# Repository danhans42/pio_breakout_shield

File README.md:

# pio_breakout_shield

Simple shield for a 39SF020, CH375/6 and Atmel ATF22V10 - for use on a Sony PlayStation console for expansion experimentation. Pretty much the basis for a modern replacement PIO cart. The parts used are(were?) easily obtainable from your online marketplace of choice.

PCB's
=====

PCB's - I used JLCPCB for production and found them very well priced, with quick delivery to me (UK). Quality was also very good, Files are provided here for the shield itself, the breakout PCB files are available on the pcsx repo - see further down this document.

Example configuration - 'fully loaded'

Parts List
==========

- SST39SF020 EEPROM (2Megabit)
- WCH 375/376 module (Either works - 376 is better as it has FAT/FAT32 support)
- Atmel ATF22V10C SPLD (GAL/PAL like device)
- 7805 type 5v regulator (i used a little module for efficiency)
- few caps for decoupling
- DIP32 socket
- PCB Pins - enough to join the bords together or use your own solution
- 68 way expansion connector (see later on for details)

When fitting the CH Module - you will notice that the connector is not correctly placed to allow for correct connection, the connect must be removed from the module and soldered from the beneath. See the image above.

PIO Breakout
============

PIO-Breakout is a seperate PCB (https://github.com/grumpycoders/pcsx-redux/wiki/PIO-Breakout), part of the PCSX-Redux project - https://pcsx-redux.consoledev.net/ which this board is designed to plug onto. You can find the files for the pcb in the repository.

The breakout board is great for expansion experimentation and highly recomended.

PIO Connector
=============

The PIO connectors can be difficult to source. See the information in the pcsx-redux wiki on the subject here, https://github.com/grumpycoders/pcsx-redux/wiki/PIO-port-replacement. Digikey link https://www.digikey.co.uk/en/products/detail/molex/0015921468/480913. They are also available on AliExpress for around $1.80 (link to follow). They do however require modification with a dremel slightly.

Alternatively if you are desperate you can source one from a faulty HK AR clone or such,

pio_breakout_shield Configuration
=================================

The board that be populated as much or as little as required. It can provide a simple 256k boot ROM so the PlayStation can boot from it - handy for Unirom etc. Alternatively you can add/program the SPLD (ATF22v10C), add a CH375/6 to it and you have a bootable cartridge that allows for USB host/device experimentation. 

The provided config (PSX_PLORER in \atf22v10c folder) for the SPLD provides the following :- 

- 256k flash @ 0x1f000000 in one block (like xplorer)
- CH37x @ 0x1f060002 (data)/0x1f060003 (cmd)
- rom enable jumper (bridge) IO15/IO14 (useful if you screw up the rom and want to recover without cart hotswapping)

This is very basic, its my intention to add some form of GPIO via the remaining pins but I currently do not have the patience with WinCUPL.
If you so chose, you could fit a 29EE020 and be able to use the standard xplorer firmware (non pro/fx) with this config.

The CH-375 supports usb device(CH372) and host mode for mass storage. However the CH376 in addition has built in FAT16/32 file system support. In future I will upload some source examples for host most such as USB Mouse examples etc. and for mass storage. 

ATF22V10C Programming
=====================

The ATF22v10c can be programmed with a TL866 programmer, as can the EEPROM itself. If you wish to play around with the configuration of the SPLD you will need to obtain WinCUPL (https://www.microchip.com/en-us/products/fpgas-and-plds/spld-cplds/pld-design-resources) to build your own equations. Unfortunately I do not know of a modern, open-source equivalent to work with these parts. Ideally use Windows or it can be got to work with Wine, as can the TL866 software.

Alternatively you can just burn the provided jed which will give you the default configuration which is similar in layout to a 256k Xplorer with the addition of the USB in the space above the ROM. (todo - document address layout). The source is provided. Its initially quite basic in scope but want to add to it to make use of the expansion IO connections provided, as well as switch functionality if desired.

Credit and Thanks
=================

To note: the PCB layout and design is the work of Nicolas Noble who was kind enough to design this for me. Thanks for this and the PIO-Breakout, without none of this would have been possible. Same for UNIROM (thanks sickle) which is indispensable for easy debugging of hardware like this. 

For more info or psx related chat - join us on psx.dev discord (http://psx.dev/)

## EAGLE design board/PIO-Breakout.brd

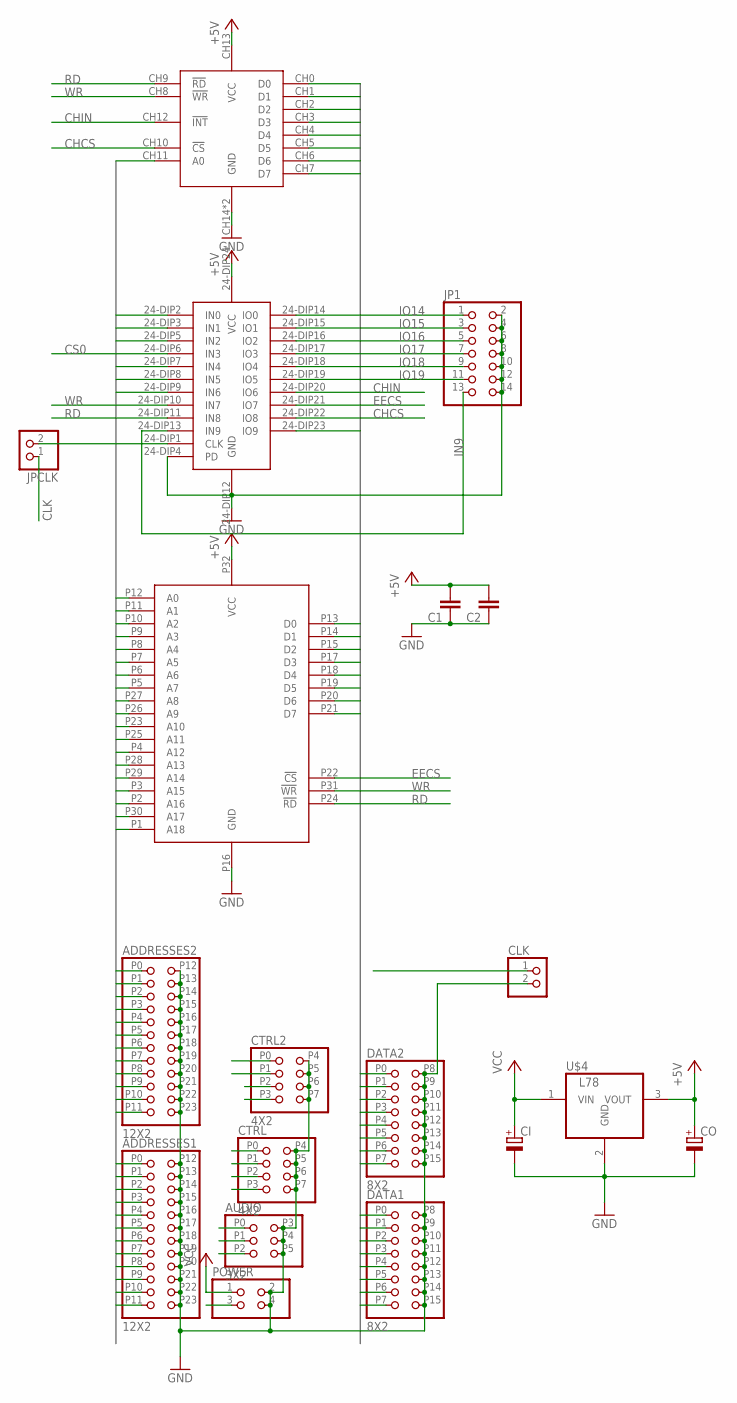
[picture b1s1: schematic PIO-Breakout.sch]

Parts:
ADDRESSES1, ADDRESSES2: 12X2
AUDIO: 3X2
C1, C2: C-EU025-024X044; C025-024X044
CI: CPOL-EUE2,5-6E; E2,5-6E
CLK: PINHD-1X2; 1X02
CO: CPOL-EUE2,5-6E; E2,5-6E
CTRL, CTRL2: 4X2
DATA1, DATA2: 8X2
JP1: PINHD-2X7; 2X07
JPCLK: PINHD-1X2; 1X02
POWER: PINHD-2X2; 2X02
U$1: AT29C040A; DIP-32
U$2: ATF22V10C-10PU; 24-DIP
U$3: CH375B-BOARD
U$4: L78; TO-220-HEATSINK

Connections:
+3V3: POWER.3
+5V: C1.2, C2.2, CO.+, U$1.P32 (VCC), U$2.24-DIP24 (VCC), U$3.CH13 (VCC), U$4.3 (VOUT)
A0: ADDRESSES1.P11, U$1.P12 (A0), U$2.24-DIP2 (IN0), U$3.CH11 (A0)
A1: ADDRESSES2.P11, U$1.P11 (A1), U$2.24-DIP3 (IN1)
A2: ADDRESSES1.P10, U$1.P10 (A2), U$2.24-DIP5 (IN2)
A3: ADDRESSES2.P10, U$1.P9 (A3)
A4: ADDRESSES1.P9, U$1.P8 (A4)
A5: ADDRESSES2.P9, U$1.P7 (A5)
A6: ADDRESSES1.P8, U$1.P6 (A6)
A7: ADDRESSES2.P8, U$1.P5 (A7)
A8: ADDRESSES1.P7, U$1.P27 (A8)
A9: ADDRESSES2.P7, U$1.P26 (A9)
A10: ADDRESSES1.P6, U$1.P23 (A10)
A11: ADDRESSES2.P6, U$1.P25 (A11)
A12: ADDRESSES1.P5, U$1.P4 (A12)
A13: ADDRESSES2.P5, U$1.P28 (A13)
A14: ADDRESSES1.P4, U$1.P29 (A14)
A15: ADDRESSES2.P4, U$1.P3 (A15)
A16: ADDRESSES1.P3, U$1.P2 (A16), U$2.24-DIP7 (IN4)
A17: ADDRESSES2.P3, U$1.P30 (A17), U$2.24-DIP8 (IN5)
A18: ADDRESSES1.P2, U$1.P1 (A18), U$2.24-DIP9 (IN6)
A19: ADDRESSES2.P2
A20: ADDRESSES1.P1
A21: ADDRESSES2.P1
A22: ADDRESSES1.P0
A23: ADDRESSES2.P0
BCLK: AUDIO.P2
CHCS: U$2.24-DIP22 (IO8), U$3.CH10 (!CS)
CHIN: U$2.24-DIP20 (IO6), U$3.CH12 (!INT)
CLK: CLK.1, JPCLK.1
CS0: CTRL.P0, U$2.24-DIP6 (IN3)
CS2: CTRL.P1
CS5: CTRL2.P0
D0: DATA1.P7, U$1.P13 (D0), U$2.24-DIP23 (IO9), U$3.CH0 (D0)
D1: DATA2.P7, U$1.P14 (D1), U$3.CH1 (D1)
D2: DATA1.P6, U$1.P15 (D2), U$3.CH2 (D2)
D3: DATA2.P6, U$1.P17 (D3), U$3.CH3 (D3)
D4: DATA1.P5, U$1.P18 (D4), U$3.CH4 (D4)
D5: DATA2.P5, U$1.P19 (D5), U$3.CH5 (D5)
D6: DATA1.P4, U$1.P20 (D6), U$3.CH6 (D6)
D7: DATA2.P4, U$1.P21 (D7), U$3.CH7 (D7)
D8: DATA1.P3
D9: DATA2.P3
D10: DATA1.P2
D11: DATA2.P2
D12: DATA1.P1
D13: DATA2.P1
D14: DATA1.P0
D15: DATA2.P0
EECS: U$1.P22 (!CS), U$2.24-DIP21 (IO7)
GND: ADDRESSES1.P12, ADDRESSES1.P13, ADDRESSES1.P14, ADDRESSES1.P15, ADDRESSES1.P16, ADDRESSES1.P17, ADDRESSES1.P18, ADDRESSES1.P19, ADDRESSES1.P20, ADDRESSES1.P21, ADDRESSES1.P22, ADDRESSES1.P23, ADDRESSES2.P12, ADDRESSES2.P13, ADDRESSES2.P14, ADDRESSES2.P15, ADDRESSES2.P16, ADDRESSES2.P17, ADDRESSES2.P18, ADDRESSES2.P19, ADDRESSES2.P20, ADDRESSES2.P21, ADDRESSES2.P22, ADDRESSES2.P23, AUDIO.P3, AUDIO.P4, AUDIO.P5, C1.1, C2.1, CI.-, CLK.2, CO.-, CTRL.P4, CTRL.P5, CTRL.P6, CTRL.P7, CTRL2.P4, CTRL2.P5, CTRL2.P6, CTRL2.P7, DATA1.P8, DATA1.P9, DATA1.P10, DATA1.P11, DATA1.P12, DATA1.P13, DATA1.P14, DATA1.P15, DATA2.P8, DATA2.P9, DATA2.P10, DATA2.P11, DATA2.P12, DATA2.P13, DATA2.P14, DATA2.P15, JP1.2, JP1.4, JP1.6, JP1.8, JP1.10, JP1.12, JP1.14, POWER.2, POWER.4, U$1.P16 (GND), U$2.24-DIP4 (PD), U$2.24-DIP12 (GND), U$3.CH14 (GND), U$3.CH15 (GND), U$4.2 (GND)
IN2: CTRL2.P1
IN9: JP1.13, U$2.24-DIP13 (IN9)
IN10: CTRL.P2
IO14: JP1.1, U$2.24-DIP14 (IO0)
IO15: JP1.3, U$2.24-DIP15 (IO1)
IO16: JP1.5, U$2.24-DIP16 (IO2)
IO17: JP1.7, U$2.24-DIP17 (IO3)
IO18: JP1.9, U$2.24-DIP18 (IO4)
IO19: JP1.11, U$2.24-DIP19 (IO5)
LRCLK: AUDIO.P1
MCLK: JPCLK.2, U$2.24-DIP1 (CLK)
RD: CTRL2.P2, U$1.P24 (!RD), U$2.24-DIP11 (IN8), U$3.CH9 (!RD)
RESET: CTRL.P3
SDIN: AUDIO.P0
VCC: CI.+, POWER.1, U$4.1 (VIN)
WR: CTRL2.P3, U$1.P31 (!WR), U$2.24-DIP10 (IN7), U$3.CH8 (!WR)

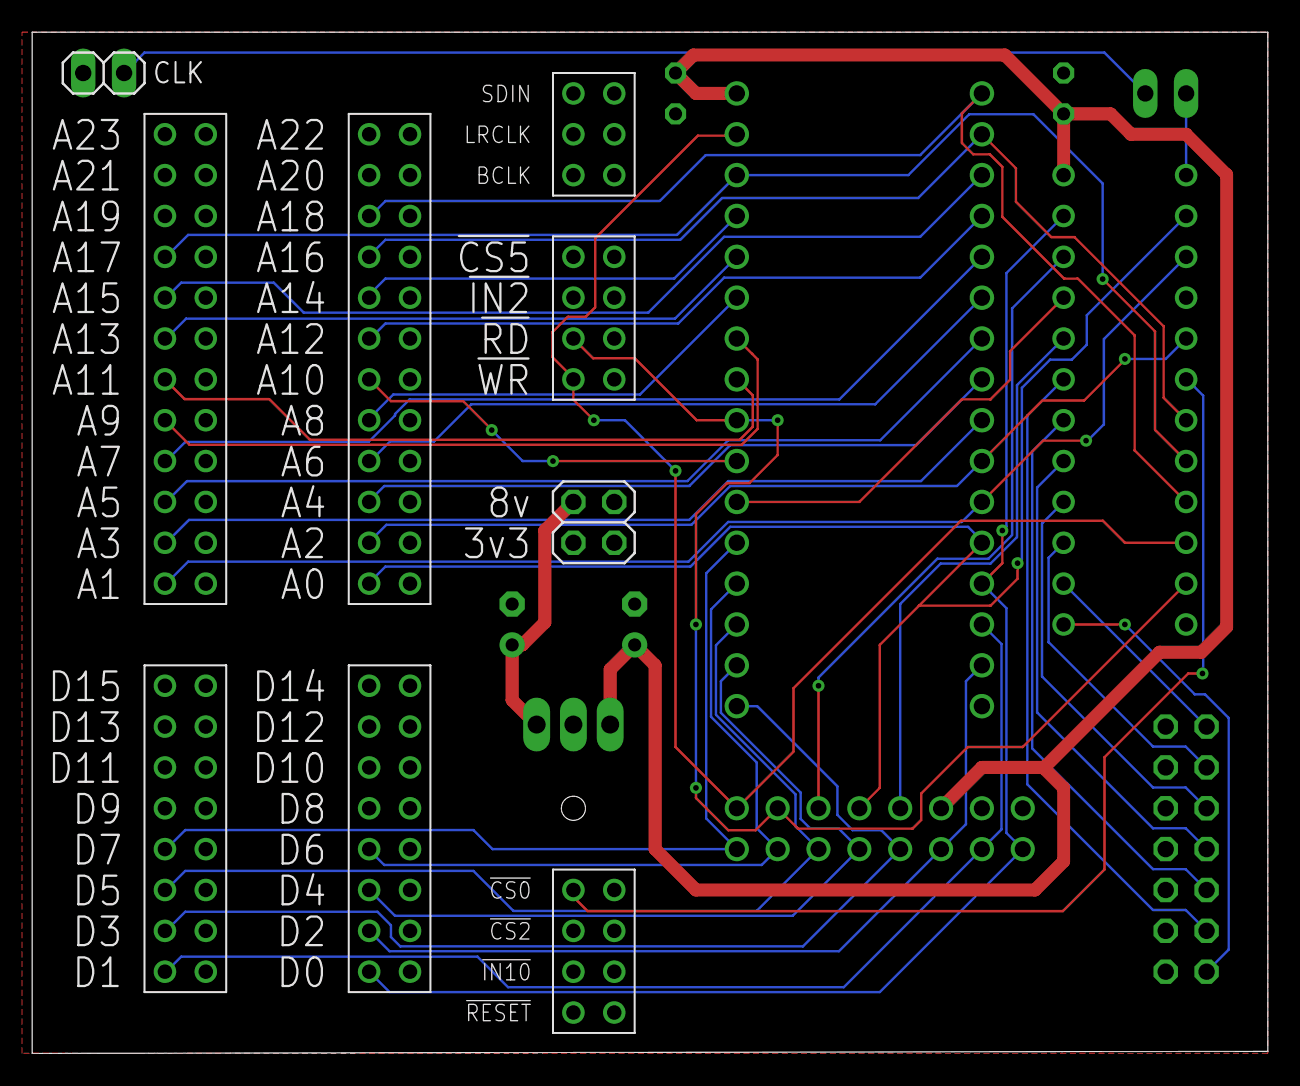
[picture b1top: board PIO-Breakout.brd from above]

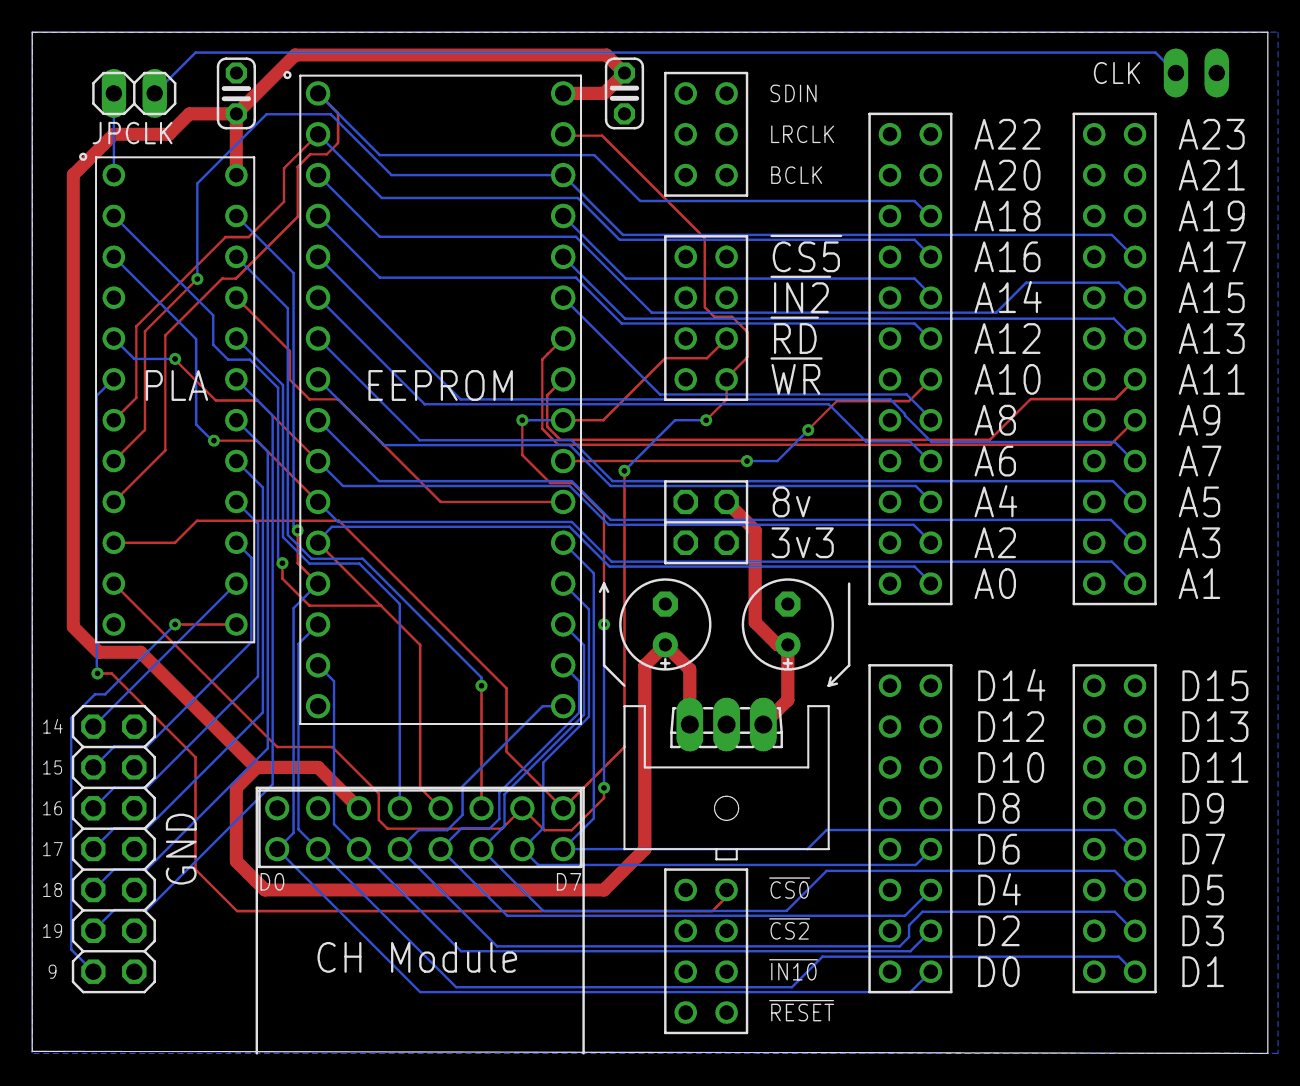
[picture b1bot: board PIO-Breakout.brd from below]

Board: 2 copper layers, 76.8 x 63.5 mm, 19 parts (10 on the bottom side), 45 nets.
